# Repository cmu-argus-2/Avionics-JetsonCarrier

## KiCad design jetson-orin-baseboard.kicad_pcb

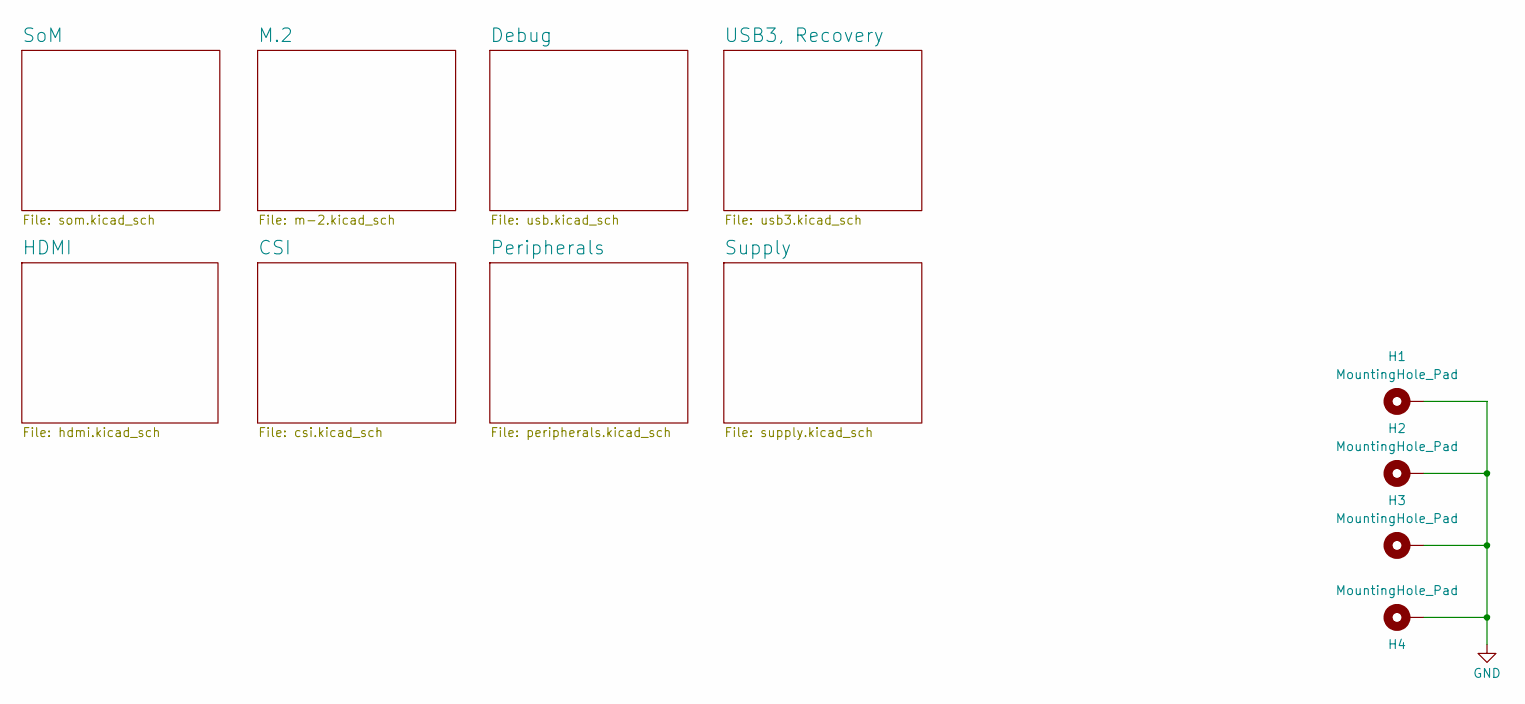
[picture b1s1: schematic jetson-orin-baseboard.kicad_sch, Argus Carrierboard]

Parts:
H1, H2, H3, H4: MountingHole_Pad; MountingHole_3.2mm_M3_Pad_Via

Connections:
GND: H1.1 (1_1), H2.1 (1_1), H3.1 (1_1), H4.1 (1_1); also elsewhere on the board

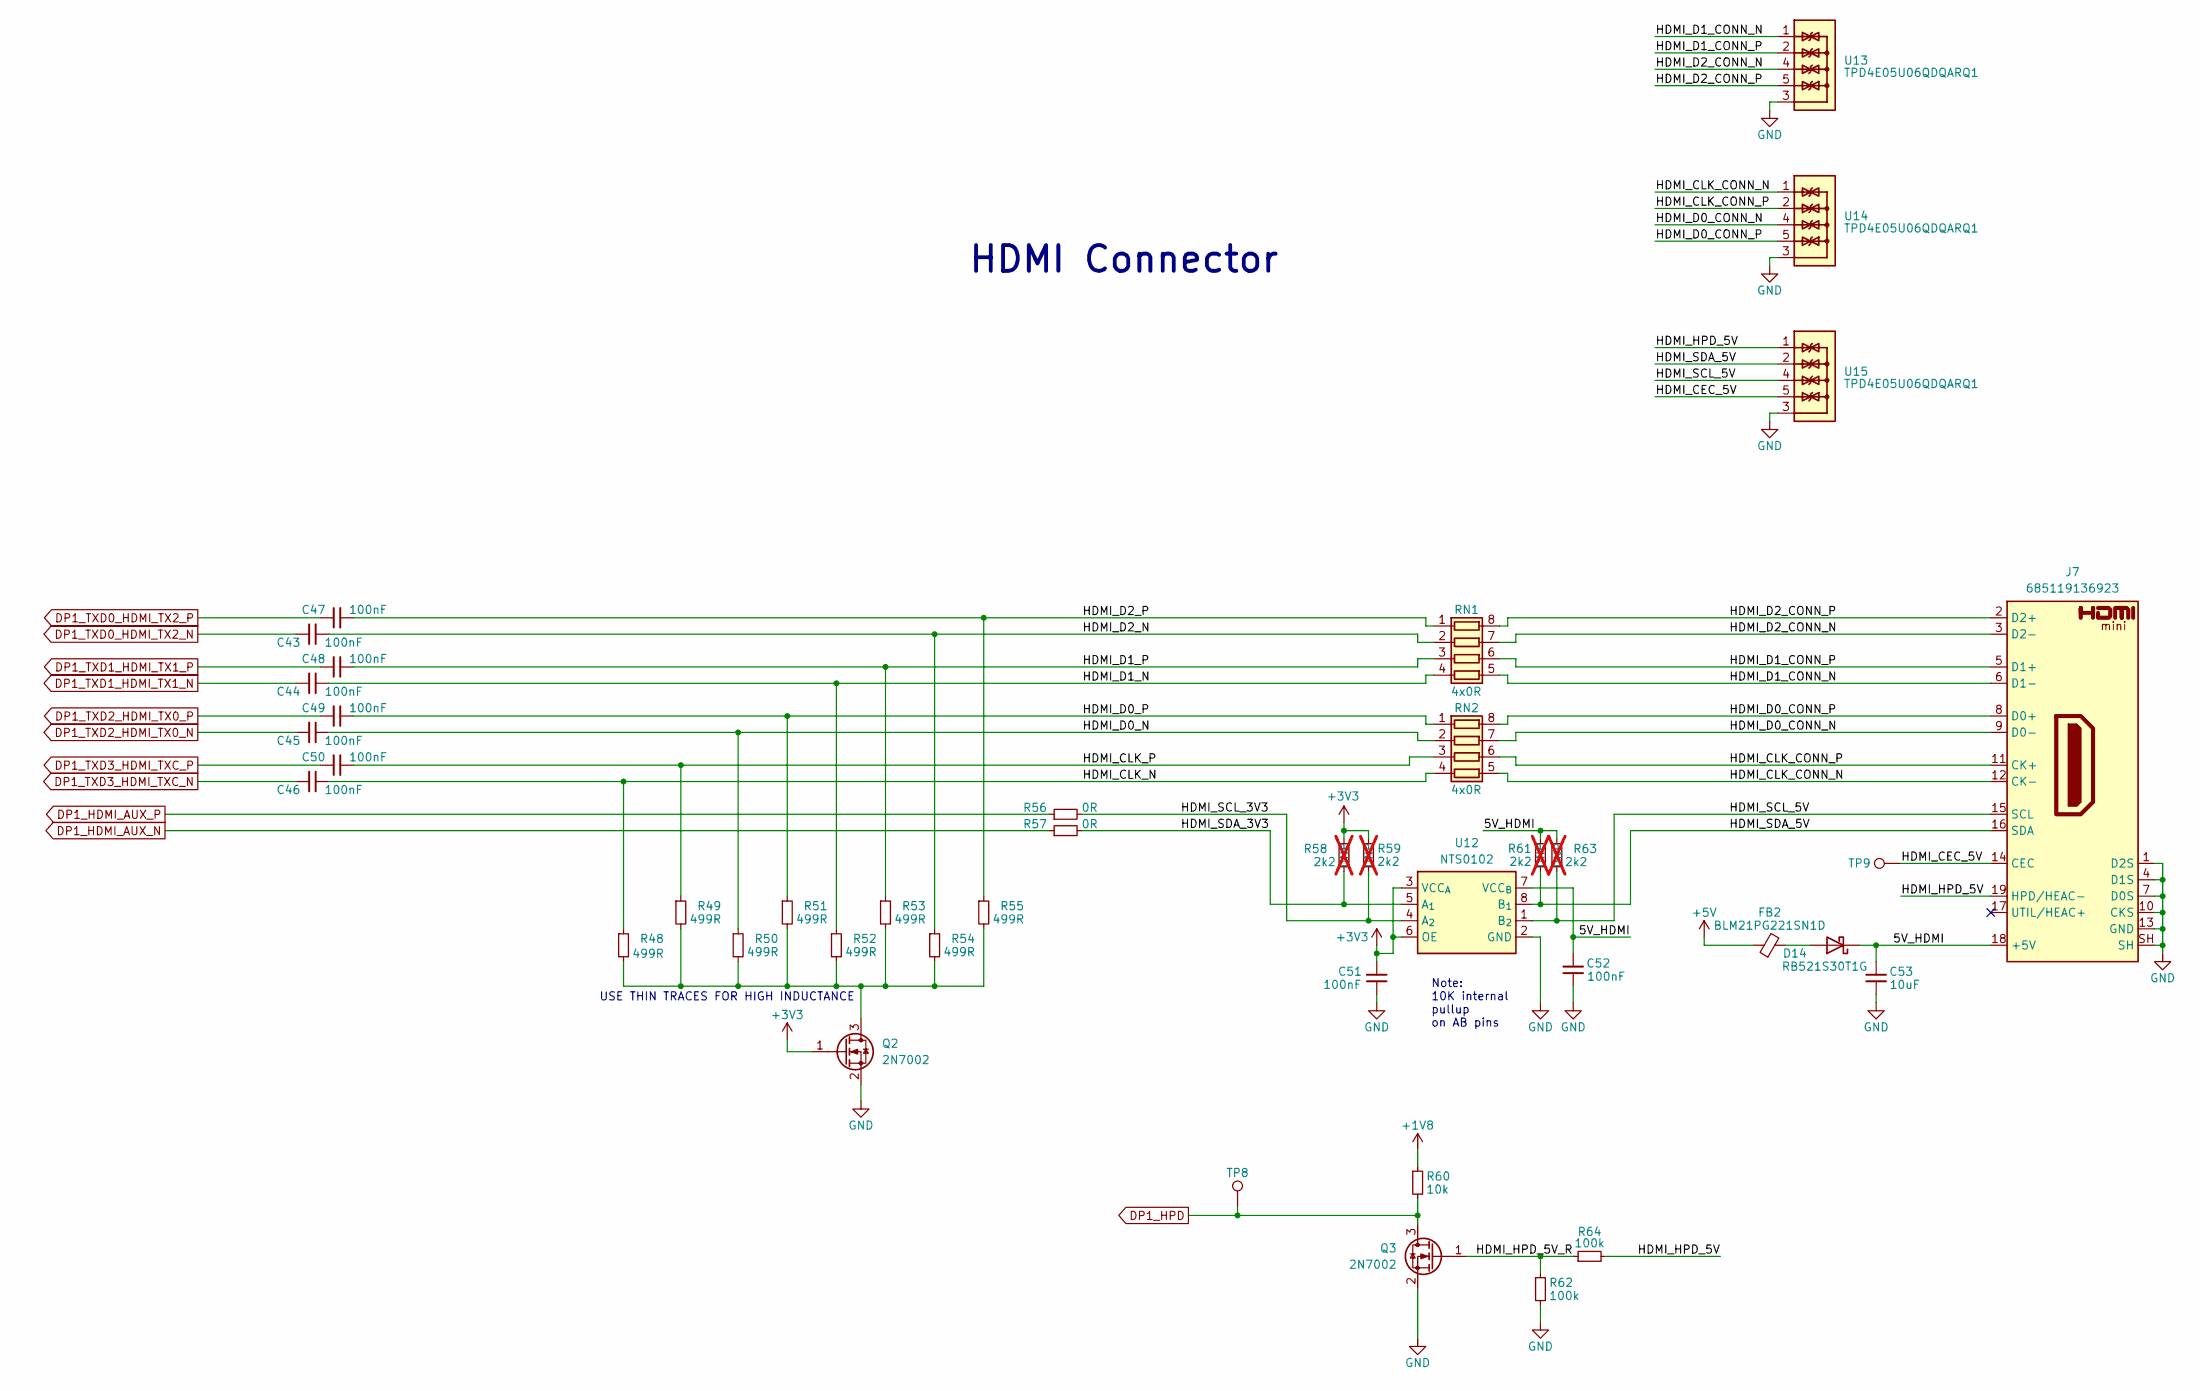
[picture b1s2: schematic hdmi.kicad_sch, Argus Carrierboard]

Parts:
C43, C44, C45, C46, C47, C48, C49, C50: 100nF; C_0402_1005Metric; MPN C85858; LCSC C307331
C51, C52: 100nF; C_0603_1608Metric; MPN C307348; LCSC C14663
C53: 10uF; C_0603_1608Metric; MPN C697423; LCSC C96446
D14: RB521S30T1G; D_SOD-523; MPN RB521S30T1G; LCSC C145179
FB2: BLM21PG221SN1D; L_0805_2012Metric; MPN C85840; LCSC C85840
J7: 685119136923; HDMI-Mini-C_Receptacle_WE_685119136923; MPN 685119136923; LCSC C2961651
Q2, Q3: 2N7002; SOT-23; LCSC C8545
R48, R49, R50, R51, R52, R53, R54, R55: 499R; R_0402_1005Metric; MPN C2076754; LCSC C4125
R56, R57: 0R; R_0402_1005Metric; MPN C190119; LCSC C17168
R58, R59, R61, R63: 2k2; R_0402_1005Metric; Tolerance 1%; MPN CR0402-FX-2201GLF; LCSC C25879; not fitted
R60: 10k; R_0603_1608Metric; MPN C2479067; LCSC C25804
R62, R64: 100k; R_0603_1608Metric; MPN C237792; LCSC C25803
RN1, RN2: 4x0R; R_Array_Concave_4x0402; MPN EXB-18VR000X; LCSC C2001
TP8, TP9: TP_0.75mm_SMD; TestPoint_Pad_D1.0mm
U12: NTS0102; NXP_XSON-8; MPN NTS0102GT; LCSC C2687851
U13, U14, U15: TPD4E05U06QDQARQ1; USON-10_TEX; MPN C81353; LCSC C81353

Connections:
+1V8: R60.1; also elsewhere on the board
+3V3: C51.1, Q2.1 (G), R58.1, R59.2, U12.3 (VCC_{A}), U12.6 (OE); also elsewhere on the board
+5V: FB2.1; also elsewhere on the board
/HDMI/5V_HDMI: C52.1, C53.1, D14.1 (K), J7.18 (+5V), R61.2, R63.1, U12.7 (VCC_{B})
/HDMI/HDMI_CEC_5V: J7.14 (CEC), TP9.1 (1_1), U15.5, U15.6
/HDMI/HDMI_CLK_CONN_N: J7.12 (CK-), RN2.5 (R4.2), U14.1, U14.10
/HDMI/HDMI_CLK_CONN_P: J7.11 (CK+), RN2.6 (R3.2), U14.2, U14.9
/HDMI/HDMI_CLK_N: C46.2, R48.1, RN2.4 (R4.1)
/HDMI/HDMI_CLK_P: C50.2, R49.1, RN2.3 (R3.1)
/HDMI/HDMI_D0_CONN_N: J7.9 (D0-), RN2.7 (R2.2), U14.4, U14.7
/HDMI/HDMI_D0_CONN_P: J7.8 (D0+), RN2.8 (R1.2), U14.5, U14.6
/HDMI/HDMI_D0_N: C45.2, R50.1, RN2.2 (R2.1)
/HDMI/HDMI_D0_P: C49.2, R51.1, RN2.1 (R1.1)
/HDMI/HDMI_D1_CONN_N: J7.6 (D1-), RN1.5 (R4.2), U13.1, U13.10
/HDMI/HDMI_D1_CONN_P: J7.5 (D1+), RN1.6 (R3.2), U13.2, U13.9
/HDMI/HDMI_D1_N: C44.2, R52.1, RN1.4 (R4.1)
/HDMI/HDMI_D1_P: C48.2, R53.1, RN1.3 (R3.1)
/HDMI/HDMI_D2_CONN_N: J7.3 (D2-), RN1.7 (R2.2), U13.4, U13.7
/HDMI/HDMI_D2_CONN_P: J7.2 (D2+), RN1.8 (R1.2), U13.5, U13.6
/HDMI/HDMI_D2_N: C43.2, R54.1, RN1.2 (R2.1)
/HDMI/HDMI_D2_P: C47.2, R55.1, RN1.1 (R1.1)
/HDMI/HDMI_HPD_5V: J7.19 (HPD/HEAC-), R64.2, U15.1, U15.10
/HDMI/HDMI_HPD_5V_R: Q3.1 (G), R62.1, R64.1
/HDMI/HDMI_SCL_3V3: R56.2, R59.1, U12.4 (A_{2})
/HDMI/HDMI_SCL_5V: J7.15 (SCL), R63.2, U12.1 (B_{2}), U15.4, U15.7
/HDMI/HDMI_SDA_3V3: R57.2, R58.2, U12.5 (A_{1})
/HDMI/HDMI_SDA_5V: J7.16 (SDA), R61.1, U12.8 (B_{1}), U15.2, U15.9
DP1_HDMI_AUX_N: R57.1; also elsewhere on the board
DP1_HDMI_AUX_P: R56.1; also elsewhere on the board
DP1_HPD: Q3.3 (D), R60.2, TP8.1 (1_1); also elsewhere on the board
DP1_TXD0_HDMI_TX2_N: C43.1; also elsewhere on the board
DP1_TXD0_HDMI_TX2_P: C47.1; also elsewhere on the board
DP1_TXD1_HDMI_TX1_N: C44.1; also elsewhere on the board
DP1_TXD1_HDMI_TX1_P: C48.1; also elsewhere on the board
DP1_TXD2_HDMI_TX0_N: C45.1; also elsewhere on the board
DP1_TXD2_HDMI_TX0_P: C49.1; also elsewhere on the board
DP1_TXD3_HDMI_TXC_N: C46.1; also elsewhere on the board
DP1_TXD3_HDMI_TXC_P: C50.1; also elsewhere on the board
GND: C51.2, C52.2, C53.2, J7.1 (D2S), J7.4 (D1S), J7.7 (D0S), J7.10 (CKS), J7.13 (GND), J7.SH, Q2.2 (S), Q3.2 (S), R62.2, U12.2 (GND), U13.3, U13.8, U14.3, U14.8, U15.3, U15.8; also elsewhere on the board
unnamed: D14.2 (A), FB2.2
unnamed: Q2.3 (D), R48.2, R49.2, R50.2, R51.2, R52.2, R53.2, R54.2, R55.2

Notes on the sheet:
USE THIN TRACES FOR HIGH INDUCTANCE
Note: 10K internal pullup on AB pins
HDMI Connector

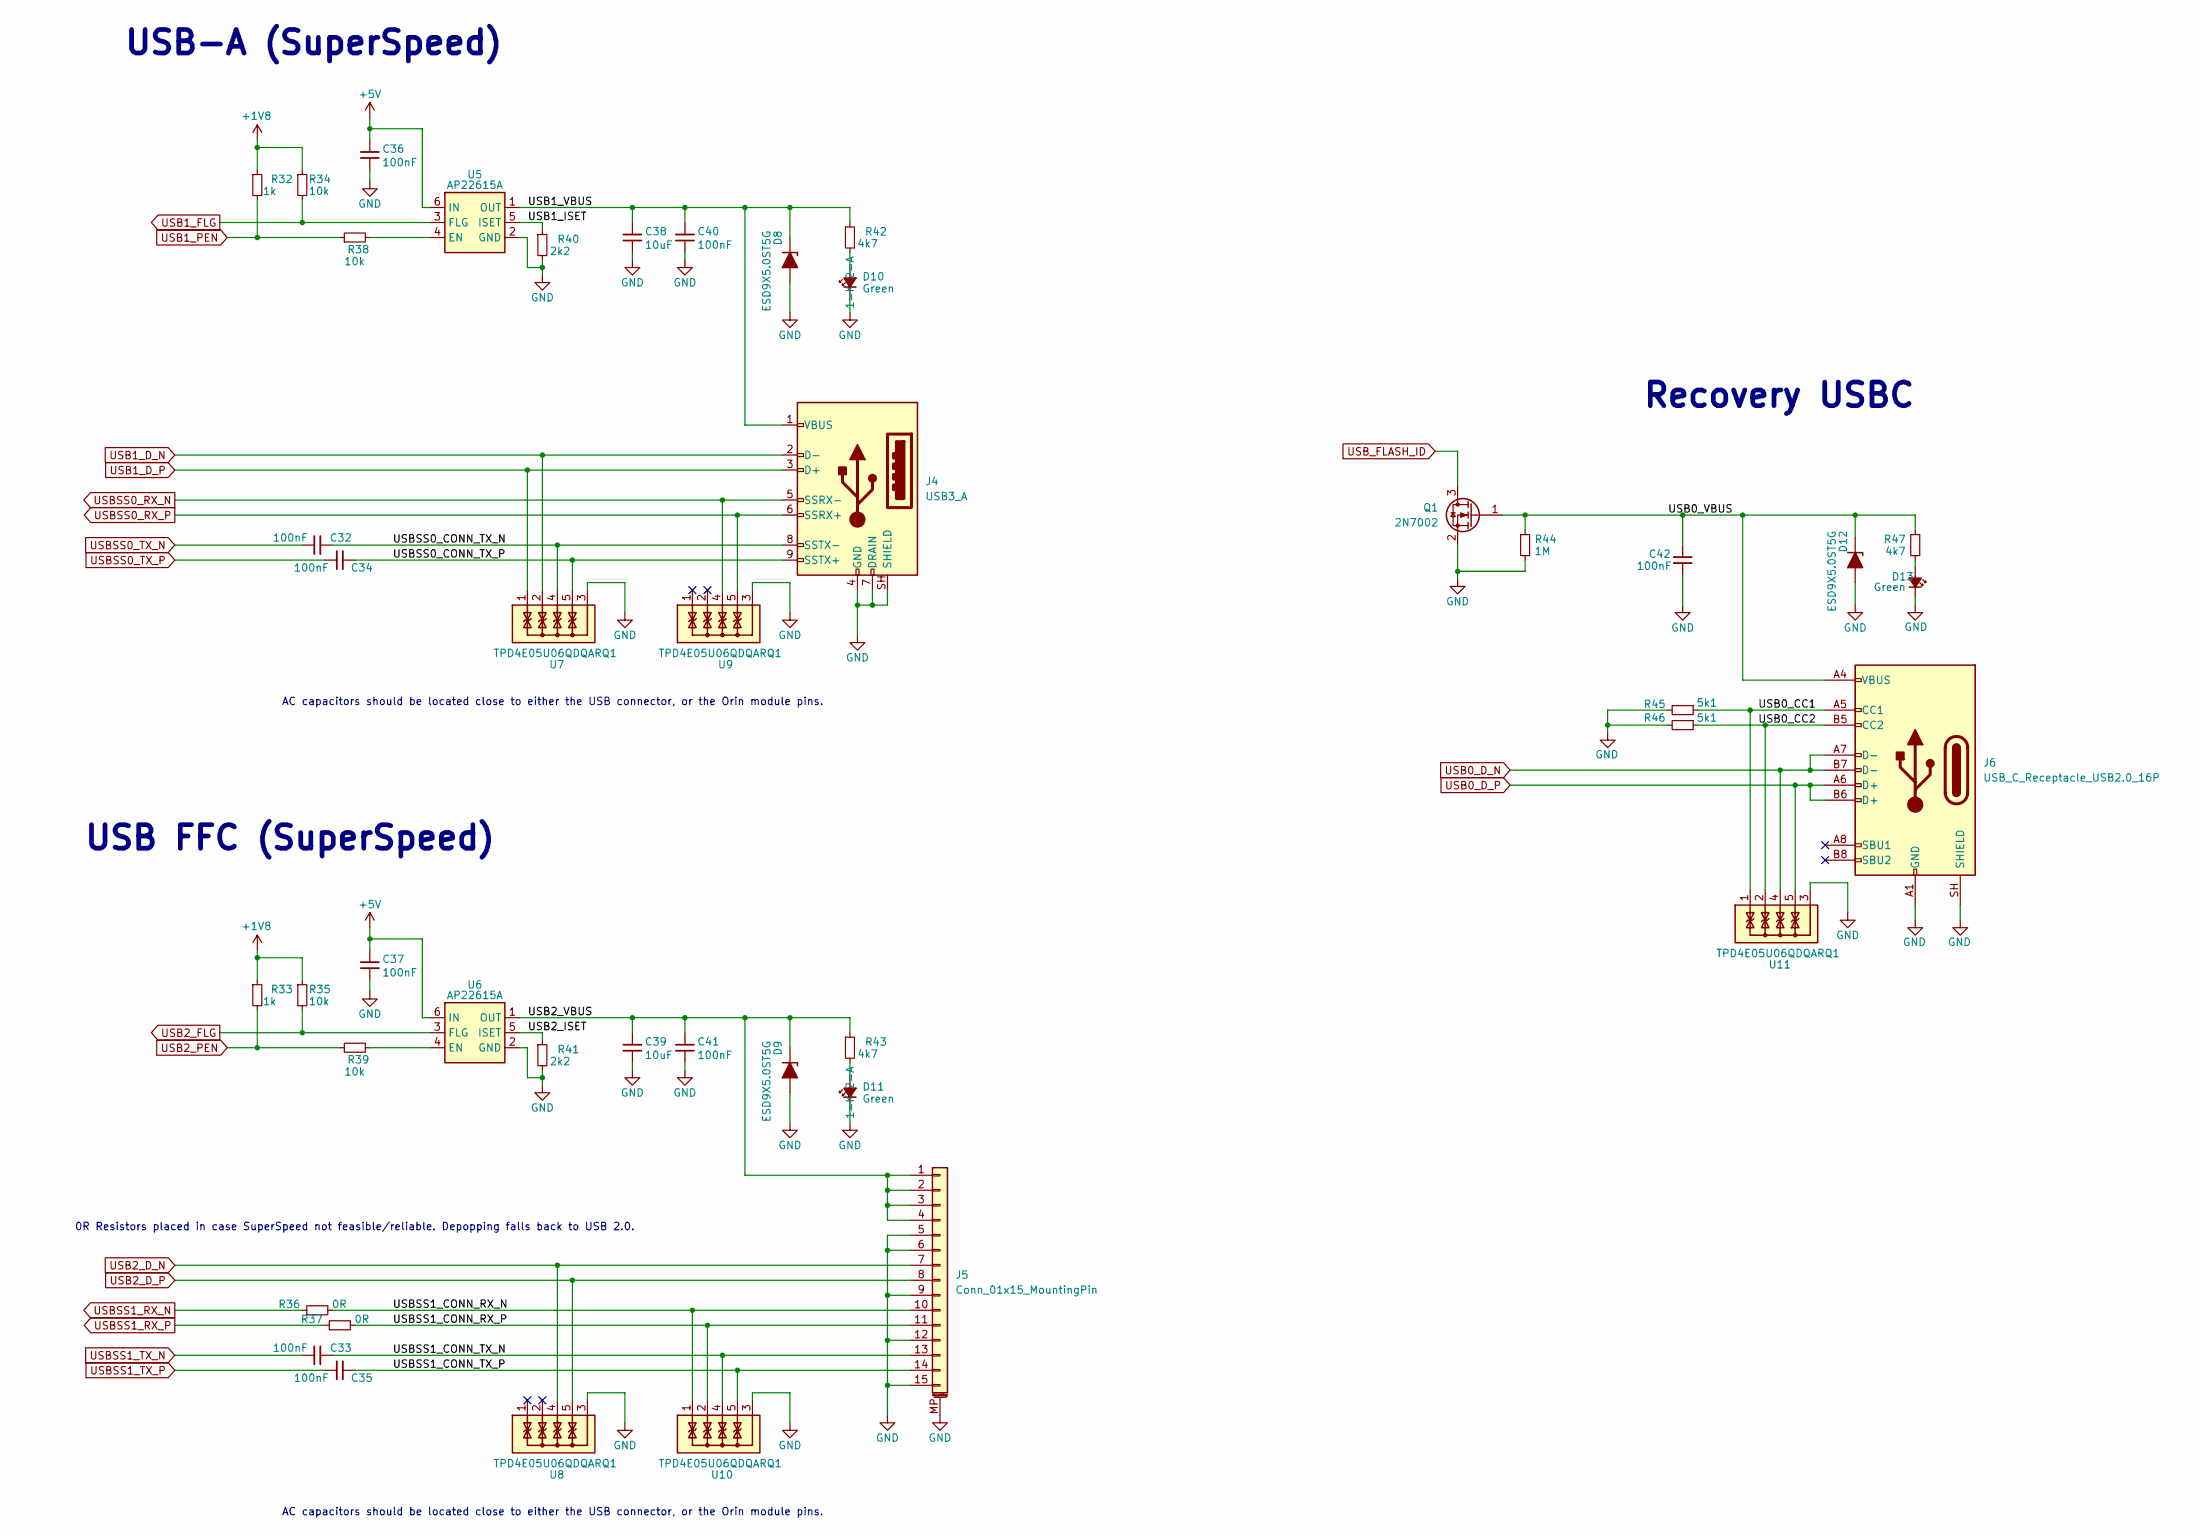
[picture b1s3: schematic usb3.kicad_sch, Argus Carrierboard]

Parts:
C32, C33, C34, C35: 100nF; C_0402_1005Metric; MPN C85858; LCSC C307331
C36, C37, C40, C41, C42: 100nF; C_0603_1608Metric; MPN C307348; LCSC C14663
C38, C39: 10uF; C_0603_1608Metric; MPN C697423; LCSC C96446
D8, D9, D12: ESD9X5.0ST5G; D_SOD-923; MPN C87910; LCSC C87910
D10, D11, D13: LED_G_0603_LTST-C190GKT; LED_0603_1608Metric; MPN C2909774; LCSC C12065
J4: USB3_A; USB-A_3.0_GSB311131HR; LCSC C473057
J5: Conn_01x15_MountingPin; Amphenol_F32Q-1A7x1-11015_1x15-1MP_P0.5mm_Horizontal
J6: USB_C_Receptacle_USB2.0_16P; USB_C_Receptacle_GCT_USB4105-xx-A_16P_TopMnt_Horizontal; LCSC C3020560
Q1: 2N7002; SOT-23; LCSC C8545
R32, R33: 1k; R_0603_1608Metric; MPN C71623; LCSC C21190
R34, R35, R38, R39: 10k; R_0603_1608Metric; MPN C71617; LCSC C25804
R36, R37: 0R; R_0402_1005Metric; MPN C190119; LCSC C17168
R40, R41: 2k2; R_0603_1608Metric; MPN C2076947; LCSC C4190
R42, R43: 4k7; R_0603_1608Metric; MPN C482193; LCSC C23162
R44: 1M; R_0603_1608Metric; MPN C844931; LCSC C22935
R45, R46: 5k1; R_0603_1608Metric; MPN C490833; LCSC C23186
R47: 4k7; R_0603_1608Metric; MPN C844931; LCSC C23162
U5, U6: AP22615A; TSOT-23-6; MPN C2680357; LCSC C2680357
U7, U8, U9, U10, U11: TPD4E05U06QDQARQ1; USON-10_TEX; MPN C81353; LCSC C81353

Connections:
+1V8: R32.1, R33.1, R34.1, R35.1; also elsewhere on the board
+5V: C36.2, C37.2, U5.6 (IN), U6.6 (IN); also elsewhere on the board
/USB3, Recovery/USB0_CC1: J6.A5 (CC1), R45.1, U11.1, U11.10
/USB3, Recovery/USB0_CC2: J6.B5 (CC2), R46.1, U11.2, U11.9
/USB3, Recovery/USB0_VBUS: C42.2, D12.1 (K), J6.A4 (VBUS), J6.A9 (VBUS), J6.B4 (VBUS), J6.B9 (VBUS), Q1.1 (G), R44.1, R47.1
/USB3, Recovery/USB1_ISET: R40.1, U5.5 (ISET)
/USB3, Recovery/USB1_VBUS: C38.2, C40.2, D8.1 (K), J4.1 (VBUS), R42.1, U5.1 (OUT)
/USB3, Recovery/USB2_ISET: R41.1, U6.5 (ISET)
/USB3, Recovery/USB2_VBUS: C39.2, C41.2, D9.1 (K), J5.1, J5.2, J5.3, J5.4, R43.1, U6.1 (OUT)
/USB3, Recovery/USBSS0_CONN_TX_N: C32.1, J4.8 (SSTX-), U7.4, U7.7
/USB3, Recovery/USBSS0_CONN_TX_P: C34.1, J4.9 (SSTX+), U7.5, U7.6
/USB3, Recovery/USBSS1_CONN_RX_N: J5.10, R36.2, U10.1, U10.10
/USB3, Recovery/USBSS1_CONN_RX_P: J5.11, R37.2, U10.2, U10.9
/USB3, Recovery/USBSS1_CONN_TX_N: C33.1, J5.13, U10.4, U10.7
/USB3, Recovery/USBSS1_CONN_TX_P: C35.1, J5.14, U10.5, U10.6
GND: C36.1, C37.1, C38.1, C39.1, C40.1, C41.1, C42.1, D8.2 (A), D9.2 (A), D10.1 (K), D11.1 (K), D12.2 (A), D13.1 (K), J4.4 (GND), J4.7 (DRAIN), J4.SH (SHIELD), J5.5, J5.6, J5.9, J5.12, J5.15, J5.MP (MountPin), J6.A1 (GND), J6.A12 (GND), J6.B1 (GND), J6.B12 (GND), J6.SH (SHIELD), Q1.2 (S), R40.2, R41.2, R44.2, R45.2, R46.2, U5.2 (GND), U6.2 (GND), U7.3, U7.8, U8.3, U8.8, U9.3, U9.8, U10.3, U10.8, U11.3, U11.8; also elsewhere on the board
unnamed: D10.2 (A), R42.2
unnamed: D11.2 (A), R43.2
unnamed: D13.2 (A), R47.2
unnamed: R38.2, U5.4 (EN)
unnamed: R39.2, U6.4 (EN)
USB0_D_N: J6.A7 (D-), J6.B7 (D-), U11.4, U11.7; also elsewhere on the board
USB0_D_P: J6.A6 (D+), J6.B6 (D+), U11.5, U11.6; also elsewhere on the board
USB1_D_N: J4.2 (D-), U7.2, U7.9; also elsewhere on the board
USB1_D_P: J4.3 (D+), U7.1, U7.10; also elsewhere on the board
USB1_FLG: R34.2, U5.3 (FLG); also elsewhere on the board
USB1_PEN: R32.2, R38.1; also elsewhere on the board
USB2_D_N: J5.7, U8.4, U8.7; also elsewhere on the board
USB2_D_P: J5.8, U8.5, U8.6; also elsewhere on the board
USB2_FLG: R35.2, U6.3 (FLG); also elsewhere on the board
USB2_PEN: R33.2, R39.1; also elsewhere on the board
USBSS0_RX_N: J4.5 (SSRX-), U9.4, U9.7; also elsewhere on the board
USBSS0_RX_P: J4.6 (SSRX+), U9.5, U9.6; also elsewhere on the board
USBSS0_TX_N: C32.2; also elsewhere on the board
USBSS0_TX_P: C34.2; also elsewhere on the board
USBSS1_RX_N: R36.1; also elsewhere on the board
USBSS1_RX_P: R37.1; also elsewhere on the board
USBSS1_TX_N: C33.2; also elsewhere on the board
USBSS1_TX_P: C35.2; also elsewhere on the board
USB_FLASH_ID: Q1.3 (D); also elsewhere on the board

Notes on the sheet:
0R Resistors placed in case SuperSpeed not feasible/reliable. Depopping falls back to USB 2.0.
USB-A (SuperSpeed)
AC capacitors should be located close to either the USB connector, or the Orin module pins.
USB FFC (SuperSpeed)
Recovery USBC

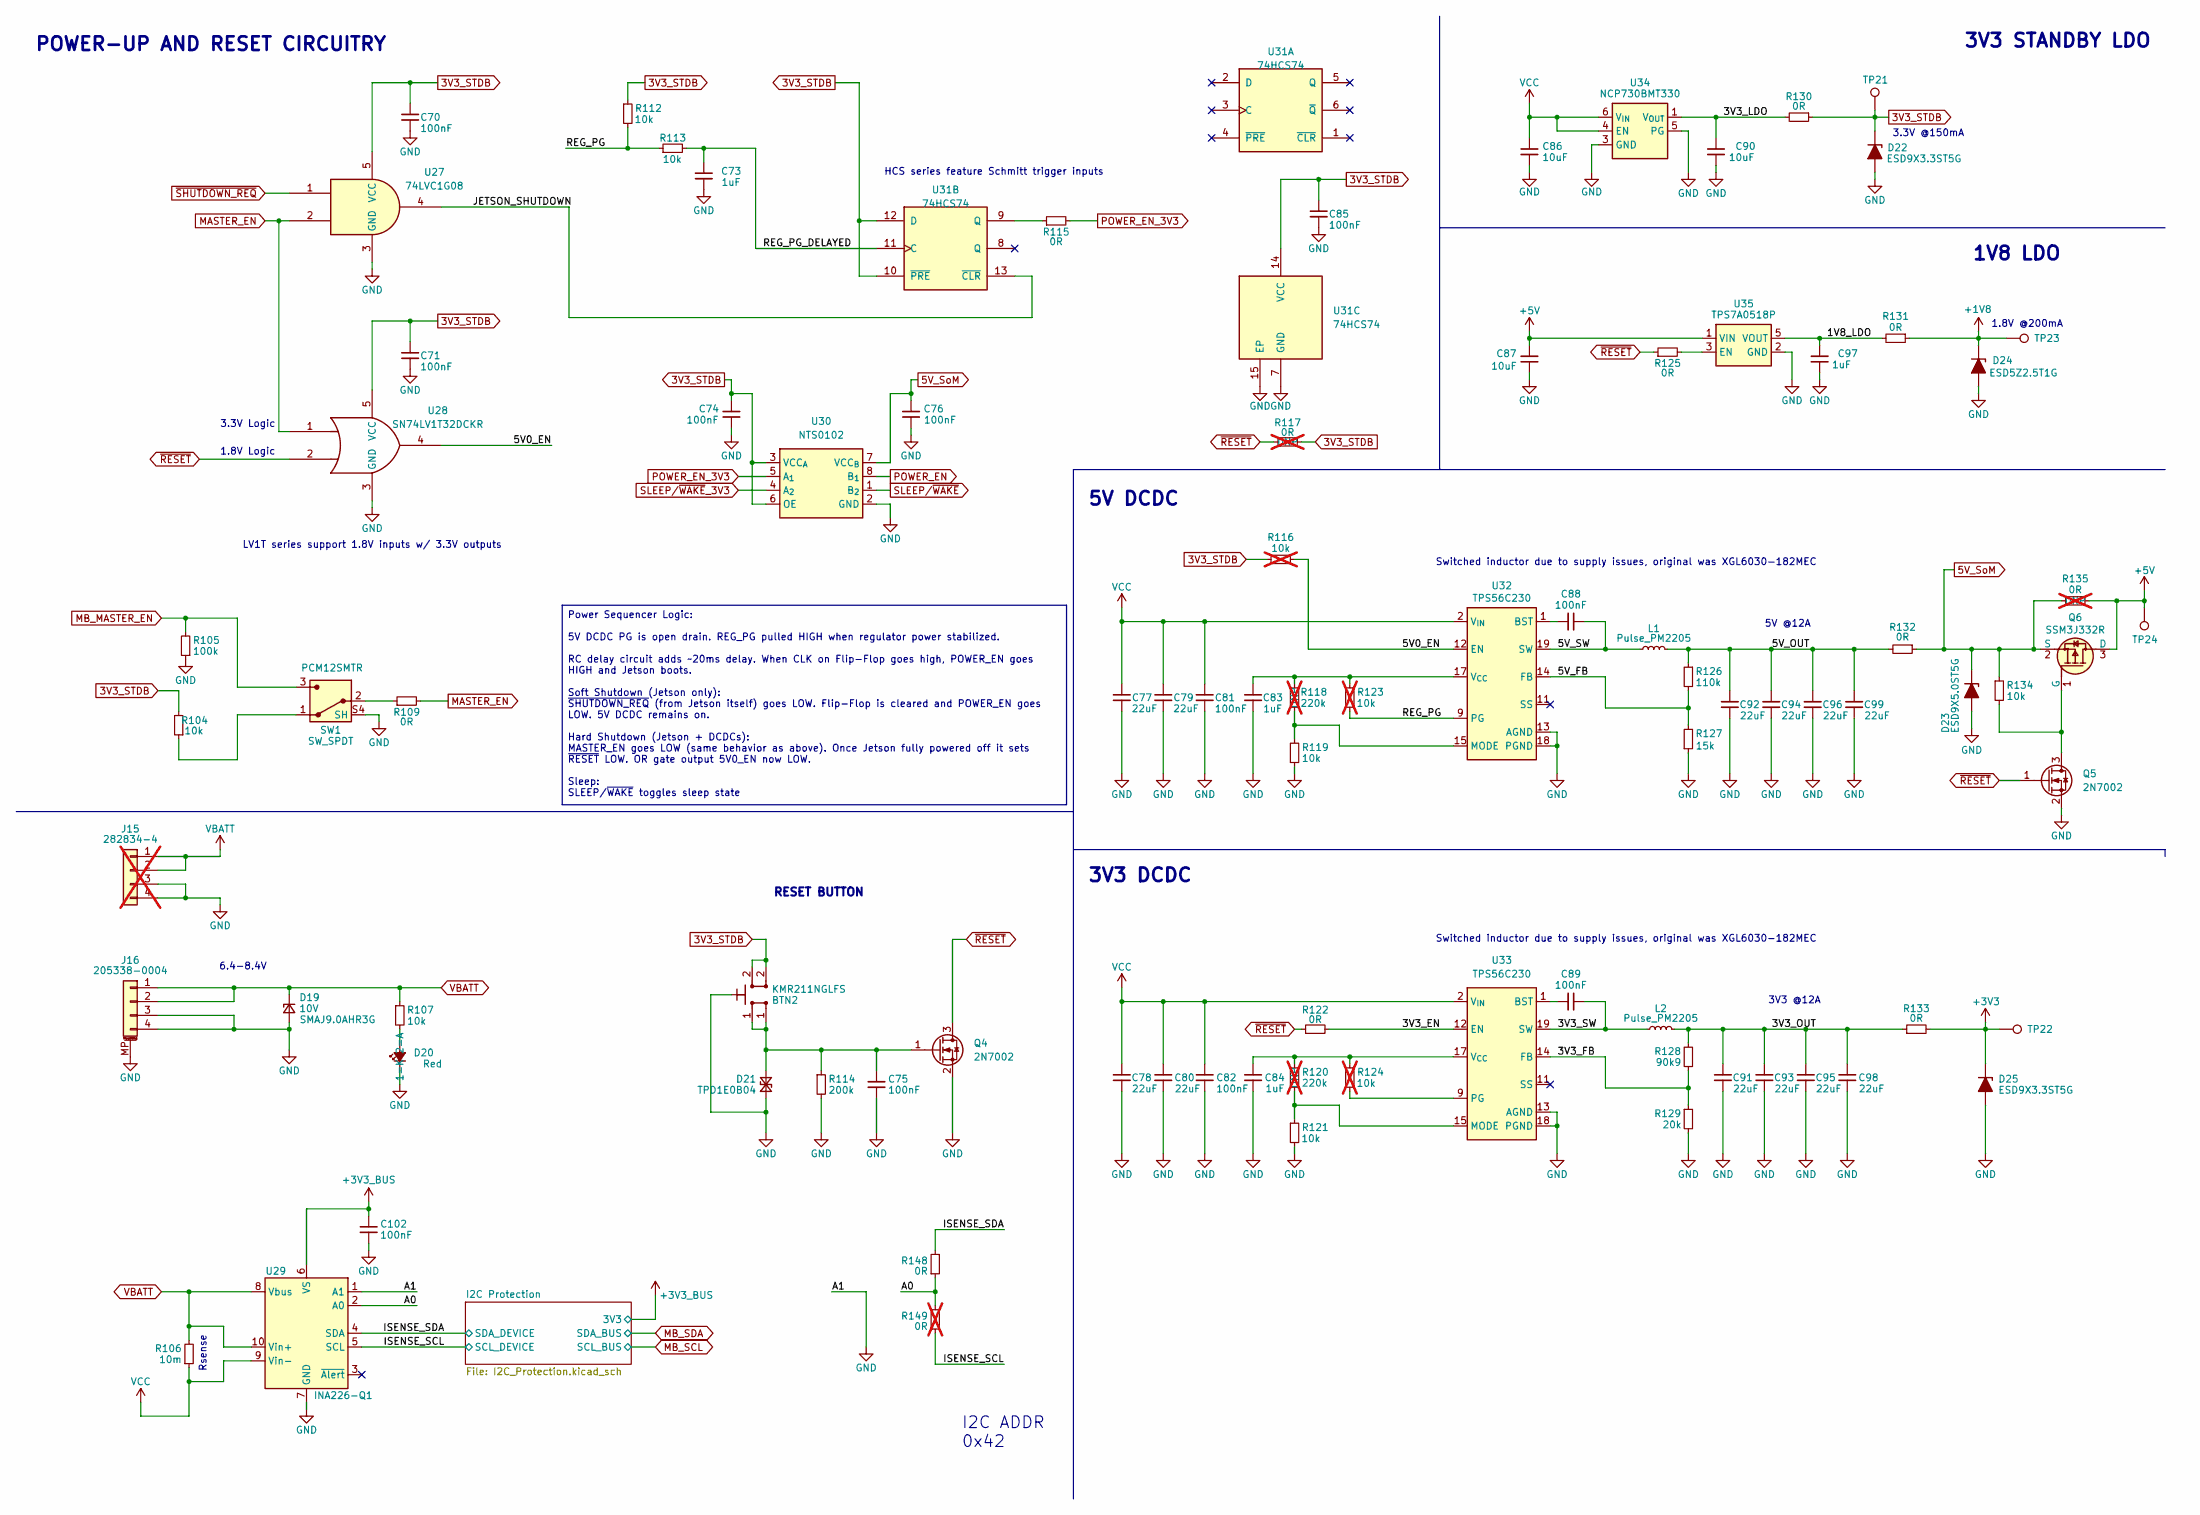
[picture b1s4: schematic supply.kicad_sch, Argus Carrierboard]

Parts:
BTN2: KMR211NGLFS; SW_Push_1P1T-SH_NO_CK_KMR2xxG; MPN C221676; LCSC C221676
C70, C71, C74, C75, C76, C81, C82, C85, C88, C89: 100nF; C_0603_1608Metric; MPN C307348; LCSC C14663
C73, C83, C84, C97: 1uF; C_0603_1608Metric; MPN C2214844; LCSC C15849
C77, C78, C79, C80: 22uF; C_0805_2012Metric; Voltage 25V; MPN CL21A226MAYNNNE; LCSC C45783
C86, C87, C90: 10uF; C_0603_1608Metric; MPN C697423; LCSC C96446
C91, C92, C93, C94, C95, C96, C98, C99: 22uF; C_0603_1608Metric; MPN C2762594; LCSC C84419
C102: 100nF; C_0603_1608Metric; MPN C2803395; LCSC C14663
D19: 10V; D_SMA; Part SMAJ9.0AHR3G; LCSC C3720382
D20: LED_G_0603_LTST-C190GKT; LED_0603_1608Metric; MPN C2909774; LCSC C2286
D21: TPD1E0B04; Texas_DPY0002A_0.6x1mm_P0.65mm; MPN C1975594; LCSC C1975594
D22, D25: ESD9X3.3ST5G; D_SOD-923; MPN C130456; LCSC C130456
D23: ESD9X5.0ST5G; D_SOD-923; MPN C87910; LCSC C87910
D24: ESD5Z2.5T1G; D_SOD-523; MPN ESD9X5.0ST5G; LCSC C890620
J15: 282834-4; TE_282834-4; not fitted
J16: 205338-0004; Molex_Pico-Lock_205338-0004_1x04-1MP_P2.00mm_Horizontal; MPN C916325; LCSC C916325
L1, L2: Pulse_PM2205; MPN XAL6030-182MEC; LCSC C2638799
Q4, Q5: 2N7002; SOT-23; LCSC C8545
Q6: SSM3J332R; SOT-23-3; MPN SSM3J332R,LF; LCSC C146367
R104, R107, R112, R113, R119, R121, R134: 10k; R_0603_1608Metric; MPN C2479067; LCSC C25804
R105: 100k; R_0603_1608Metric; MPN C2479067; LCSC C25803
R106: 10m; R_2512_6332Metric; MPN C840621; LCSC C108943
R109, R115: 0R; R_0603_1608Metric; MPN C190119; LCSC C21189
R114: 200k; R_0603_1608Metric; MPN C118142; LCSC C25811
R116, R123, R124: 10k; R_0603_1608Metric; MPN C2479067; LCSC C25804; not fitted
R117: 0R; R_0402_1005Metric; MPN ERJ2GE0R00X; LCSC C17168; not fitted
R118, R120: 220k; R_0603_1608Metric; Tolerance 1%; MPN CR0402-FX-2203GLF; LCSC C22961; not fitted
R122, R125, R130, R131, R148: 0R; R_0603_1608Metric; MPN C844915; LCSC C21189
R126: 110k; R_0603_1608Metric; MPN C473255; LCSC C25574
R127: 15k; R_0603_1608Metric; MPN C844742; LCSC C22809
R128: 90k9; R_0603_1608Metric; MPN C403390; LCSC C23129
R129: 20k; R_0603_1608Metric; MPN C844923; LCSC C4184
R132, R133: 0R; R_0805_2012Metric; MPN C844934; LCSC C17477
R135: 0R; R_0805_2012Metric; MPN PMR03EZPJ000; LCSC C17477; not fitted
R149: 0R; R_0603_1608Metric; MPN C844915; LCSC C21189; not fitted
SW1: SW_SPDT; SW_SPDT_PCM12; MPN PCM12SMTR; LCSC C221841
TP21, TP22, TP23, TP24: TP_0.75mm_SMD; TestPoint_Pad_D1.0mm
U27: 74LVC1G08; SOT-353_SC-70-5; LCSC C7832
U28: SN74LV1T32DCKR; SOT-353_SC-70-5; LCSC C470953
U29: INA226-Q1; TSSOP-10_3x3mm_P0.5mm; LCSC C2653835
U30: NTS0102; NXP_XSON-8; MPN NTS0102GT; LCSC C2687851
U31: 74HCS74; DHWQFN-14-1EP_2.5x3mm_P0.5mm_EP1x1.5mm; LCSC C2916506
U32, U33: TPS56C230; QFN-20-1EP_3x3mm_P0.45mm; MPN C1849534; LCSC C1849534
U34: NCP730BMT330; WSON-6-1EP_2x2mm_P0.65mm; MPN C892821; LCSC C892821
U35: TPS7A0518P; SOT-23-5; MPN C2862322; LCSC C2862322

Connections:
3V3_STDB: BTN2.2, C70.1, C71.1, C74.1, C85.1, D22.1 (K), R104.2, R112.1, R116.2, R117.2, R130.1, TP21.1 (1_1), U27.5 (VCC), U28.5 (VCC), U30.3 (VCC_{A}), U30.6 (OE), U31.10 (~PRE), U31.12 (D), U31.14 (VCC); also elsewhere on the board
5V_SoM: C76.1, D23.1 (K), Q6.2 (S), R132.1, R134.1, R135.1, U30.7 (VCC_{B}); also elsewhere on the board
+1V8: D24.1 (K), R131.1, TP23.1 (1_1); also elsewhere on the board
+3V3: D25.1 (K), R133.2, TP22.1 (1_1); also elsewhere on the board
+3V3_BUS: C102.2, U29.6 (VS); also elsewhere on the board
+5V: C87.1, Q6.3 (D), R135.2, TP24.1 (1_1), U35.1 (VIN); also elsewhere on the board
/Supply/1V8_LDO: C97.1, R131.2, U35.5 (VOUT)
/Supply/3V3_EN: R122.2, U33.12 (EN)
/Supply/3V3_FB: R128.1, R129.1, U33.14 (FB)
/Supply/3V3_LDO: C90.1, R130.2, U34.1 (V_{OUT})
/Supply/3V3_OUT: C91.1, C93.1, C95.1, C98.1, L2.2, R128.2, R133.1
/Supply/3V3_SW: C89.1, L2.1, U33.6 (SW), U33.19 (SW), U33.20 (SW)
/Supply/5V0_EN: R116.1, U28.4, U32.12 (EN)
/Supply/5V_FB: R126.2, R127.2, U32.14 (FB)
/Supply/5V_OUT: C92.1, C94.1, C96.1, C99.1, L1.2, R126.1, R132.2
/Supply/5V_SW: C88.1, L1.1, U32.6 (SW), U32.19 (SW), U32.20 (SW)
/Supply/A0: R148.1, R149.2, U29.2 (A0)
/Supply/ISENSE_SCL: R149.1, U29.5 (SCL); also elsewhere on the board
/Supply/ISENSE_SDA: R148.2, U29.4 (SDA); also elsewhere on the board
/Supply/JETSON_SHUTDOWN: U27.4, U31.13 (~CLR)
/Supply/REG_PG: R112.2, R113.1, R123.2, U32.9 (PG)
/Supply/REG_PG_DELAYED: C73.1, R113.2, U31.11 (C)
GND: BTN2.SH, C70.2, C71.2, C73.2, C74.2, C75.1, C76.2, C77.1, C78.2, C79.1, C80.2, C81.2, C82.2, C83.2, C84.1, C85.2, C86.2, C87.2, C90.2, C91.2, C92.2, C93.2, C94.2, C95.2, C96.2, C97.2, C98.2, C99.2, C102.1, D19.2 (A), D20.1 (K), D21.1 (A1), D22.2 (A), D23.2 (A), D24.2 (A), D25.2 (A), J15.3, J15.4, J16.3, J16.4, J16.MP (MountPin), Q4.2 (S), Q5.2 (S), R105.1, R114.2, R119.1, R121.2, R127.1, R129.2, SW1.S1 (SH), SW1.S2 (SH), SW1.S3 (SH), SW1.S4 (SH_S4), U27.3 (GND), U28.3 (GND), U29.1 (A1), U29.7 (GND), U30.2 (GND), U31.7 (GND), U31.15 (EP), U32.7 (PGND), U32.8 (PGND), U32.13 (AGND), U32.18 (PGND), U32.21 (PGND), U33.7 (PGND), U33.8 (PGND), U33.13 (AGND), U33.18 (PGND), U33.21 (PGND), U34.3 (GND), U34.5 (PG), U34.7 (GND), U35.2 (GND); also elsewhere on the board
MASTER_EN: R109.2, U27.2, U28.1
MB_MASTER_EN: R105.2, SW1.3; also elsewhere on the board
unnamed: D20.2 (A), R107.2
unnamed: BTN2.1, C75.2, D21.2 (A2), Q4.1 (G), R114.1
unnamed: Q5.3 (D), Q6.1 (G), R134.2
unnamed: R104.1, SW1.1
unnamed: R109.1, SW1.2
unnamed: R115.1, U31.9 (Q)
unnamed: C88.2, U32.1 (BST)
unnamed: R118.2, R119.2, U32.15 (MODE)
unnamed: C83.1, R118.1, R123.1, U32.17 (V_{CC})
unnamed: C89.2, U33.1 (BST)
unnamed: R120.1, R121.1, U33.15 (MODE)
unnamed: R124.2, U33.9 (PG)
unnamed: C84.2, R120.2, R124.1, U33.17 (V_{CC})
unnamed: R125.2, U35.3 (EN)
POWER_EN: U30.8 (B_{1}); also elsewhere on the board
POWER_EN_3V3: R115.2, U30.5 (A_{1})
SLEEP/~WAKE: U30.1 (B_{2}); also elsewhere on the board
SLEEP/~WAKE_3V3: U30.4 (A_{2}); also elsewhere on the board
VBATT: D19.1 (K), J15.1, J15.2, J16.1, J16.2, R106.2, R107.1, U29.8 (Vbus), U29.10 (Vin+); also elsewhere on the board
VCC: C77.2, C78.1, C79.2, C80.1, C81.1, C82.1, C86.1, R106.1, U29.9 (Vin-), U32.2 (V_{IN}), U32.3 (V_{IN}), U32.4 (V_{IN}), U32.5 (V_{IN}), U33.2 (V_{IN}), U33.3 (V_{IN}), U33.4 (V_{IN}), U33.5 (V_{IN}), U34.4 (EN), U34.6 (V_{IN})
~RESET: Q4.3 (D), Q5.1 (G), R117.1, R122.1, R125.1, U28.2; also elsewhere on the board
~SHUTDOWN_REQ: U27.1; also elsewhere on the board

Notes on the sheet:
5V @12A
Switched inductor due to supply issues, original was XGL6030-182MEC
3.3V Logic
3V3 STANDBY LDO
3.3V @150mA
LV1T series support 1.8V inputs w/ 3.3V outputs
1V8 LDO
5V DCDC
POWER-UP AND RESET CIRCUITRY
3V3 @12A
6.4-8.4V
3V3 DCDC
1.8V Logic
1.8V @200mA
HCS series feature Schmitt trigger inputs
Rsense
RESET BUTTON
I2C ADDR 0x42
Power Sequencer Logic: 5V DCDC PG is open drain. REG_PG pulled HIGH when regulator power stabilized. RC delay circuit adds ~20ms delay. When CLK on Flip-Flop goes high, POWER_EN goes HIGH and Jetson boots. Soft Shutdown (Jetson only): ~{SHUTDOWN_REQ} (from Jetson itself) goes LOW. Flip-Flop is clea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

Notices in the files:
parts and their libraries:
License: Apache-2.0
License: MIT
